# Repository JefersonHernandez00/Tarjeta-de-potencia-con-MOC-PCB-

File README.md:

# Tarjeta-de-potencia-con-MOC-PCB

Power card with MOC, made in Kicad, tested and ready to send to manufacture and use.

### DESCRIPTION

Optocoupled power card to control AC loads with any controller such as arduino or pic this is a very useful card because it can be used in any project that controls AC allowing you to modulate your project and make work more presentable and easy to operate ...

### TECHNICAL DETAILS / COMPONENTS

Details in the list of materials available for download!

(TO-220AB isolated)

15 A---700V

-40 to 125°C

approximate values depending on the Triac

### LEARN / TOPIC / BUILD INSTRUCTIONS

It is a very easy to use card with its specified DC inputs and AC outputs with its general AC connector, then it is to activate each DC input with a logic 1 to activate the load of the corresponding AC output ...

[PCB on PCBWay](https://www.pcbway.com/project/shareproject/Tarjeta_de_potencia_optoacoplada.html)

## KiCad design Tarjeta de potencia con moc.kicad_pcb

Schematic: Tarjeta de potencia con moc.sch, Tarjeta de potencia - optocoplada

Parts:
D1, D2, D3, D4, D5: LED; LED_D3.0mm
J1, J2, J3, J4, J5, J6, J7, J8, J9, J10, J11: Linea; TerminalBlock_bornier-2_P5.08mm
R1, R2, R3, R4, R5, R6, R7, R8, R9, R10: 10K; R_Axial_DIN0207_L6.3mm_D2.5mm_P10.16mm_Horizontal
U1, U2, U3, U4, U5: MOC3021M; DIP-6_W7.62mm
U6, U7, U8, U9, U10: Q7015L5; TO-220-3_Vertical

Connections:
GND: D1.1, D2.1, D3.1, D4.1, D5.1, J1.1, J2.1, J3.1, J4.1, J5.1, U1.2, U2.2, U3.2, U4.2, U5.2
unnamed: D1.2, J1.2, R1.2
unnamed: D2.2, J2.2, R2.2
unnamed: D3.2, J3.2, R3.2
unnamed: D4.2, J4.2, R4.2
unnamed: D5.2, J5.2, R5.2
unnamed: J6.1, U6.1
unnamed: J7.1, U7.1
unnamed: J8.1, U8.1
unnamed: J9.1, U9.1
unnamed: J10.1, U10.1
unnamed: J6.2, J7.2, J8.2, J9.2, J10.2, J11.1
unnamed: J11.2, U1.4, U2.4, U3.4, U4.4, U5.4, U6.2, U7.2, U8.2, U9.2, U10.2
unnamed: R1.1, U1.1
unnamed: R2.1, U2.1
unnamed: R3.1, U3.1
unnamed: R4.1, U4.1
unnamed: R5.1, U5.1
unnamed: R6.1, U6.3
unnamed: R6.2, U1.6
unnamed: R7.1, U7.3
unnamed: R7.2, U2.6
unnamed: R8.1, U8.3
unnamed: R8.2, U3.6
unnamed: R9.1, U9.3
unnamed: R9.2, U4.6
unnamed: R10.1, U10.3
unnamed: R10.2, U5.6

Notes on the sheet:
Fase
Neutro
Señal de activación
Carga AC

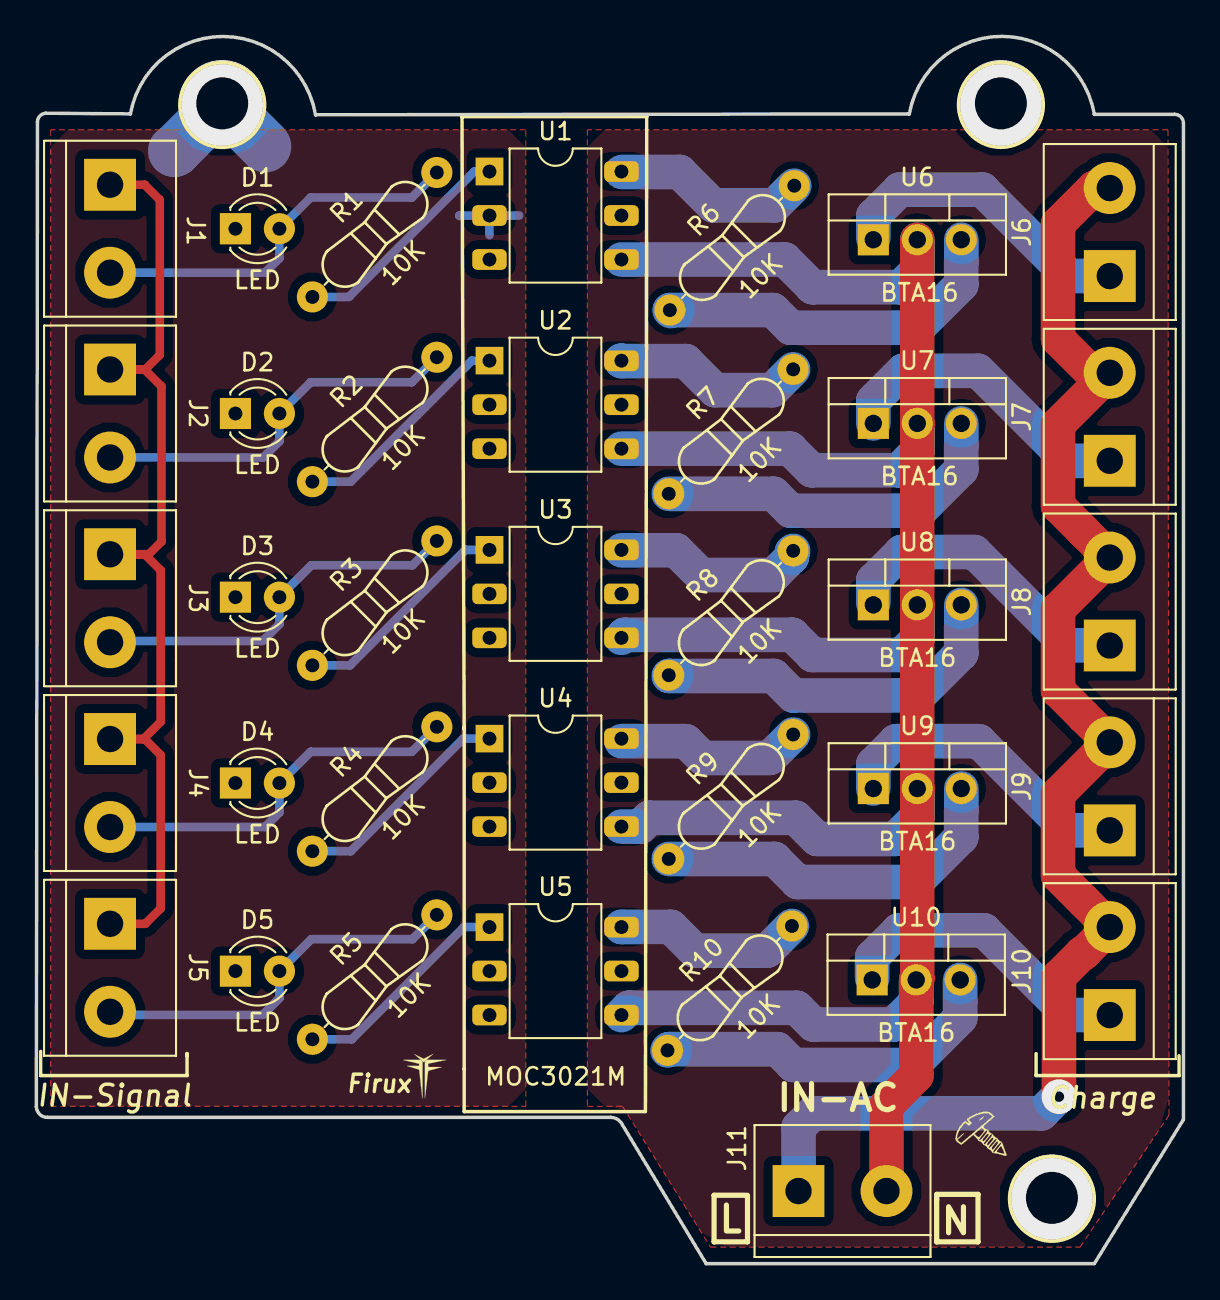
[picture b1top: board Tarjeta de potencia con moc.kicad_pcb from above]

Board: 2 copper layers, 66.2 x 70.9 mm, 36 parts (0 on the bottom side), 28 nets.

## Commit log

2022-06-05 Power card with MOC, made in Kicad, tested and ready to send to manufacture and use.
